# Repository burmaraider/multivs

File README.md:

# Multi VS. Game Boards

## Description

This board design will allow you to run up to 8 games per side on a Nintendo Vs. board. Larger games like wrecking crew will limit the amount of games you can have on this.

## Whats included

This repo includes the following:
- GERBER Files needed to send to a fab house
- Eagle CAD files so that you can modify this design further, and/or fix things. (both 7.x and 9.x files)
- Parts List (see bom.txt)
- **An application to package up ROM's so that you can burn to some flash memory** - coming soon

## Why do this?

Things should be free in this world. And if you don't agree, well, okay then.

## Final note

If you like this, please share and spread the love. If you have fixed anything, please share and upload back here.

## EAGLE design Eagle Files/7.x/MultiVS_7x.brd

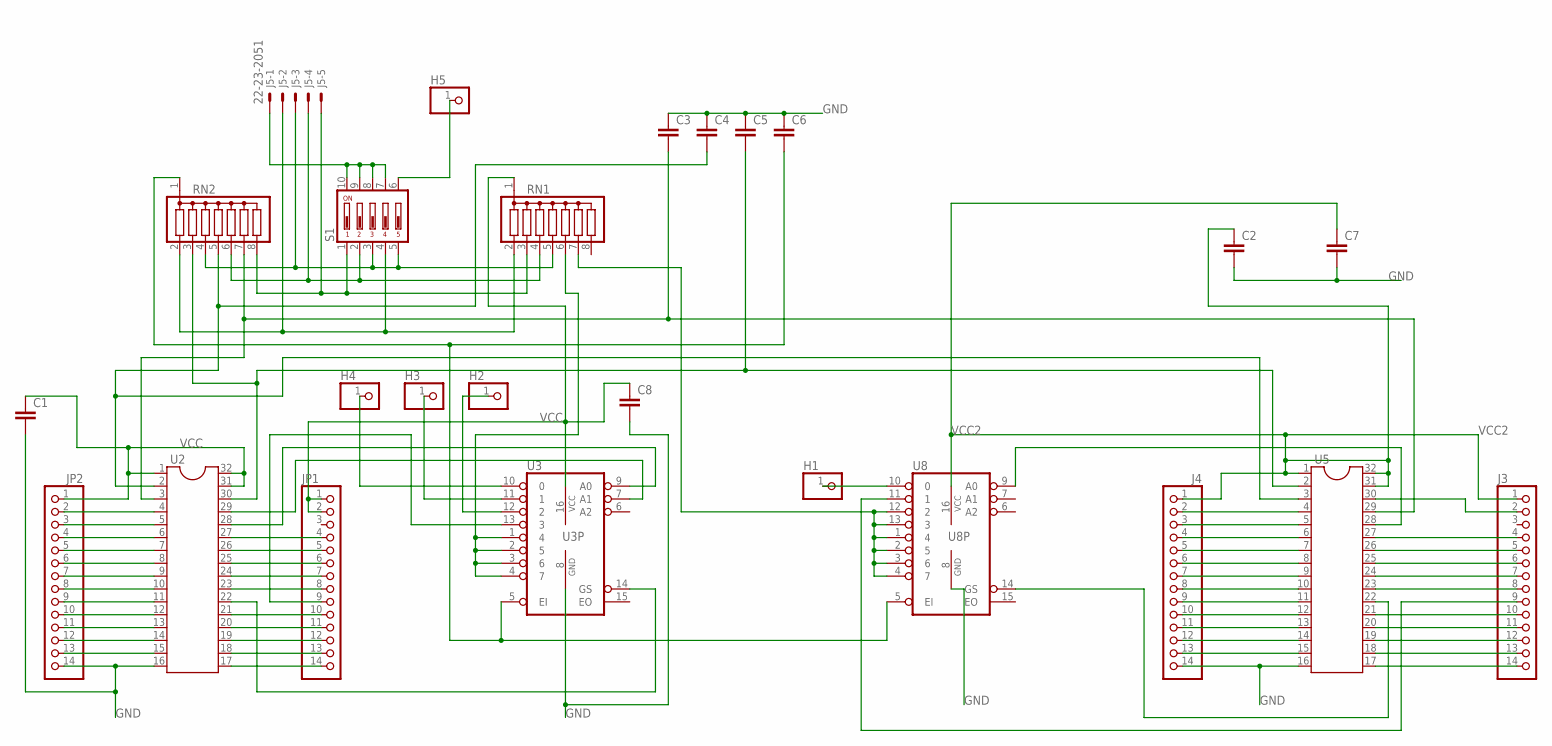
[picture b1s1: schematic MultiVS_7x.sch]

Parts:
C1, C2, C3, C4, C5, C6, C7, C8: C2.5/4; C2.5-4
H1, H2, H3, H4, H5: PINHD-1X1; 1X01
J3, J4: PINHD-1X14; 1X14
J5: 22-23-2051
JP1, JP2: PINHD-1X14; 1X14
RN1, RN2: G07R; SIL8
S1: DIP05YL
U2, U5: DIL32
U3, U8: 74LS148N; DIL16

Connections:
GND: C1.2, C2.2, C3.1, C4.1, C5.1, C6.1, C7.2, C8.2, J4.14, JP2.14, U2.16, U3.8 (GND), U5.16, U8.8 (GND)
unnamed: H1.1, U8.10 (0)
unnamed: H2.1, U3.12 (2)
unnamed: H3.1, U3.11 (1)
unnamed: H4.1, U3.10 (0)
unnamed: H5.1, S1.6
unnamed: JP2.13, U2.15
unnamed: JP2.12, U2.14
unnamed: JP2.11, U2.13
unnamed: JP2.10, U2.12
unnamed: JP2.9, U2.11
unnamed: JP2.8, U2.10
unnamed: JP2.7, U2.9
unnamed: JP2.6, U2.8
unnamed: JP2.5, U2.7
unnamed: JP2.4, U2.6
unnamed: JP2.3, U2.5
unnamed: J5.5, RN1.3, RN2.8, S1.1
unnamed: JP2.2, U2.4
unnamed: C3.2, RN2.7, U2.3, U5.29
unnamed: JP1.14, U2.17
unnamed: JP1.13, U2.18
unnamed: JP1.12, U2.19
unnamed: JP1.11, U2.20
unnamed: JP1.10, U2.21
unnamed: JP1.9, U3.13 (3)
unnamed: JP1.8, U2.23
unnamed: U2.22, U3.14 (GS)
unnamed: JP1.7, U2.24
unnamed: JP1.6, U2.25
unnamed: JP1.5, U2.26
unnamed: JP1.4, U2.27
unnamed: U2.28, U3.9 (A0)
unnamed: U2.29, U3.7 (A1)
unnamed: C4.2, RN2.5, U2.2, U5.3
unnamed: C5.2, RN2.3, U2.30, U5.2
unnamed: RN1.6, U3.1 (4), U3.2 (5), U3.3 (6), U3.4 (7)
unnamed: C6.2, RN2.1, U3.5 (EI), U8.5 (EI)
unnamed: U5.28, U8.9 (A0)
unnamed: J3.2, U5.30
unnamed: J5.1, S1.7, S1.8, S1.9, S1.10
unnamed: J5.4, RN1.4, RN2.6, S1.2
unnamed: J5.3, RN1.5, RN2.4, S1.3, S1.5
unnamed: RN1.7, U8.1 (4), U8.2 (5), U8.3 (6), U8.4 (7), U8.12 (2), U8.13 (3)
unnamed: J3.9, U8.11 (1)
unnamed: J4.13, U5.15
unnamed: J4.12, U5.14
unnamed: J5.2, RN1.2, RN2.2, S1.4
unnamed: J4.11, U5.13
unnamed: J4.10, U5.12
unnamed: J4.9, U5.11
unnamed: J4.8, U5.10
unnamed: J4.7, U5.9
unnamed: J4.6, U5.8
unnamed: J4.5, U5.7
unnamed: J4.4, U5.6
unnamed: J4.3, U5.5
unnamed: J4.2, U5.4
unnamed: J3.14, U5.17
unnamed: J3.13, U5.18
unnamed: J3.12, U5.19
unnamed: J3.11, U5.20
unnamed: J3.10, U5.21
unnamed: U5.22, U8.14 (GS)
unnamed: J3.8, U5.23
unnamed: J3.7, U5.24
unnamed: J3.6, U5.25
unnamed: J3.5, U5.26
unnamed: J3.4, U5.27
VCC: C1.1, C8.1, JP1.1, JP1.2, JP2.1, RN1.1, U2.1, U2.31, U2.32, U3.16 (VCC)
VCC2: C2.1, C7.1, J3.1, J4.1, U5.1, U5.31, U5.32, U8.16 (VCC)

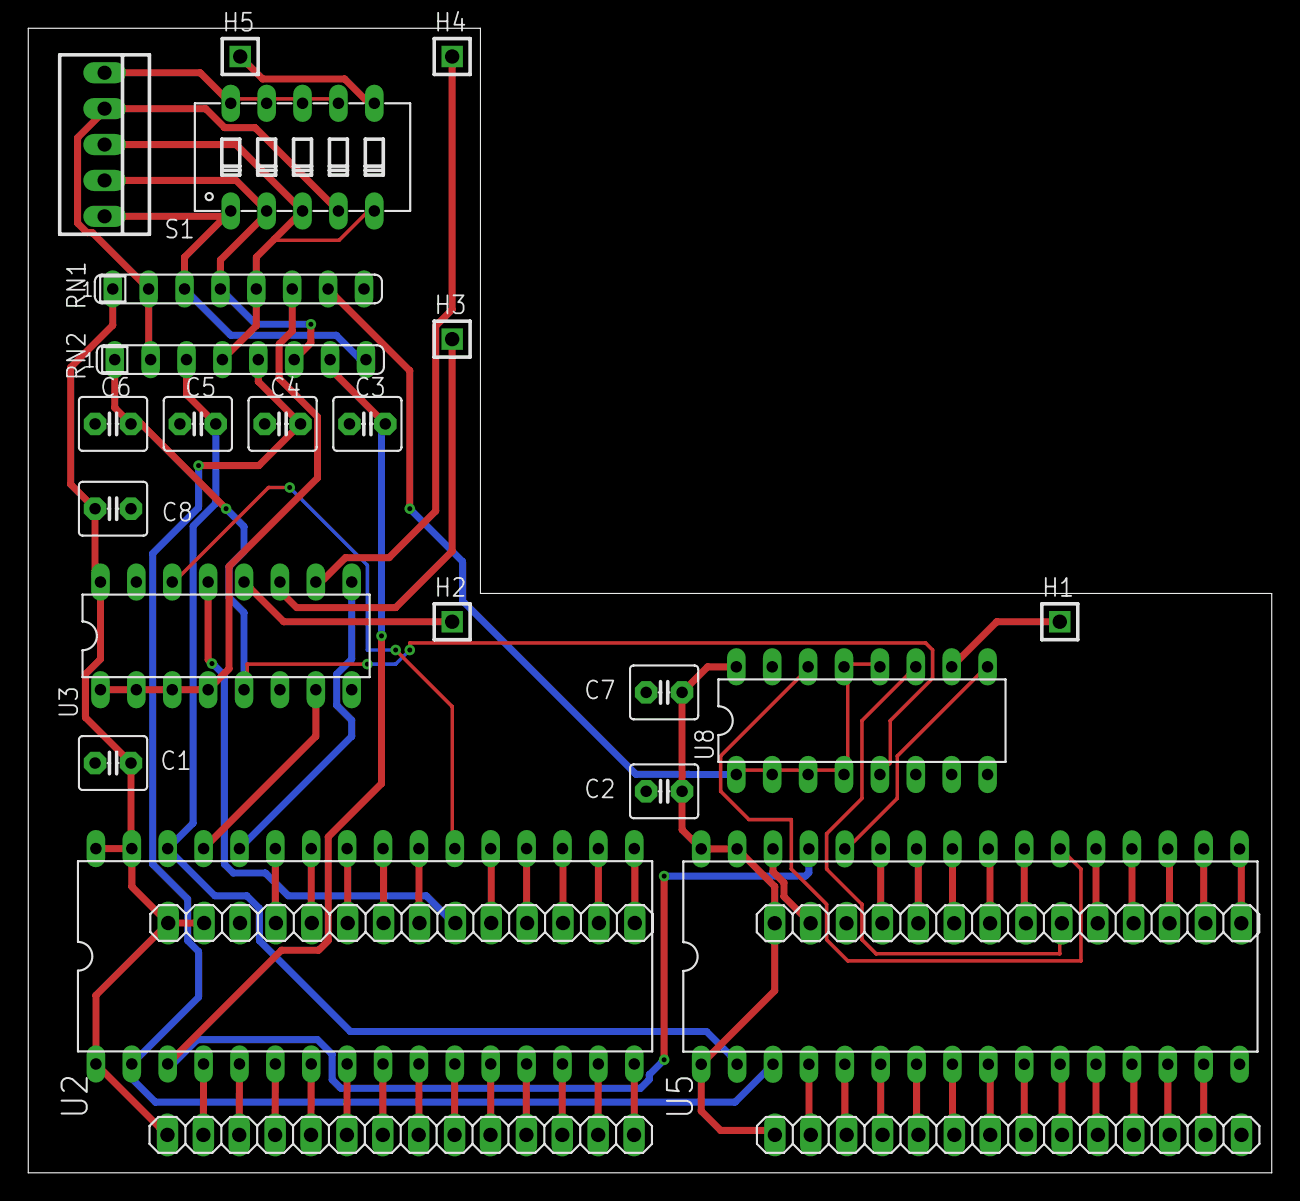
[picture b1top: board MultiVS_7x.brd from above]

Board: 2 copper layers, 88.0 x 81.0 mm, 25 parts (0 on the bottom side), 71 nets.
